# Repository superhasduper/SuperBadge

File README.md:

# SuperBadge
This is a remake of the PCB-badge. in collaboration with PCBway an incredible PCB Manufacturing company.
thanks to PCBway I have been able to remake the PCB badge I previously made and improve upon it a little.
PCBway is great for any prototypes or projects you may have in mind since it offers a lot different posibilities and configurations to customize and make your PCB just how you imagined it. It is very fast and of very high cuality(https://www.pcbway.com) check my instagram(@superhasduper)for pictures of the final product.You can also buy this pcb design directly from PCBway and forget about all the hastle and exporting gerber files and such(https://www.pcbway.com/project/shareproject/Superhasduper_superbadge.html)
This PCB was designed in kicad so I recommend viewing the files in kicad.

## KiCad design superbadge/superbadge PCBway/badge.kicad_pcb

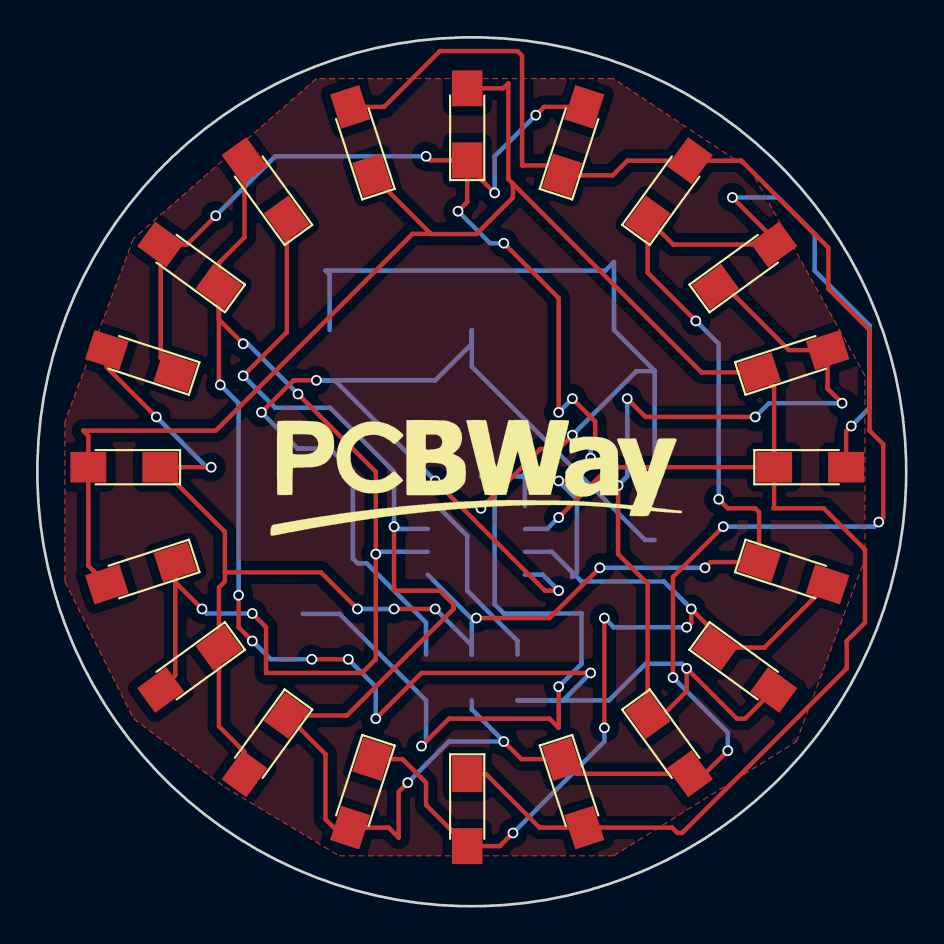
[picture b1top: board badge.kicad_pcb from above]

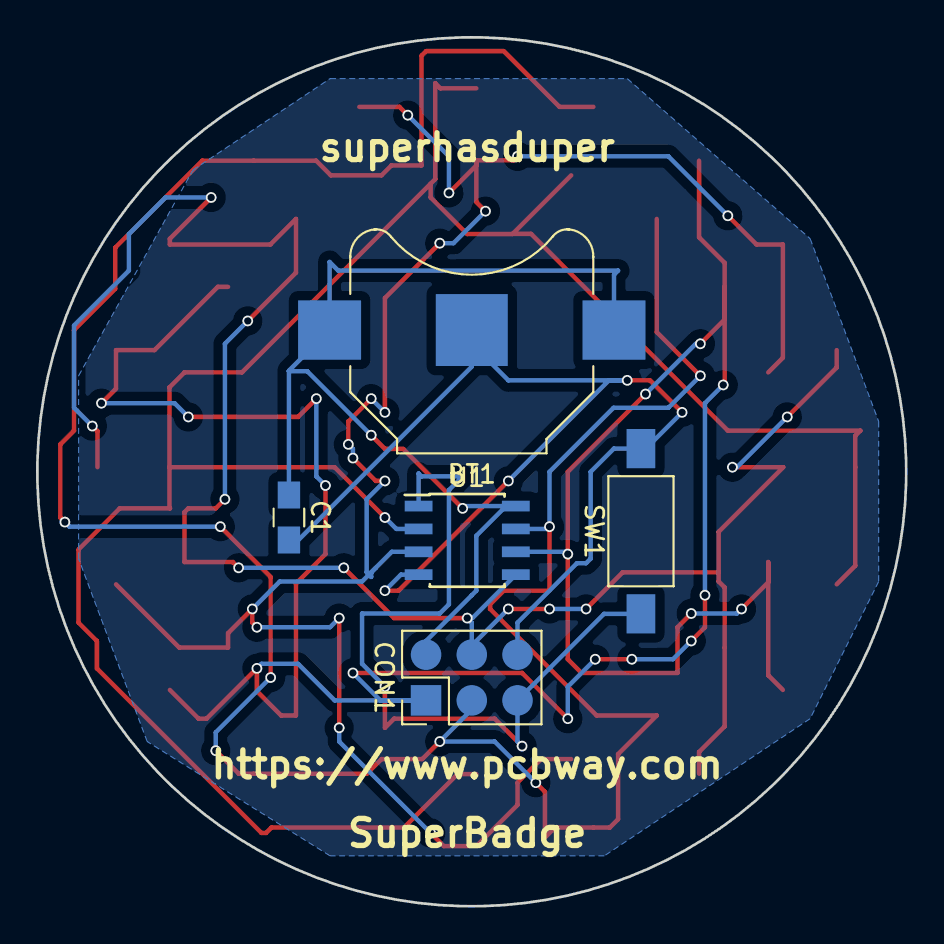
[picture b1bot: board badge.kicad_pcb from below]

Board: 2 copper layers, 48.3 x 48.3 mm, 25 parts (5 on the bottom side), 8 nets.

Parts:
BT1: Battery_Cell; Keystone_3000_1x12mm-CoinCell
C1: CP; C_0805_HandSoldering
CON1: AVR-ISP-6; Pin_Header_Straight_2x03_Pitch2.54mm
D1, D2, D3, D4, D5, D6, D7, D8, D9, D10, D11, D12, D13, D14, D15, D16, D17, D18, D19, D20: LED; LED_1206_HandSoldering
SW1: SW_Push; SW_SPST_FSMSM
U1: ATTINY85-20SU; SOIC-8_3.9x4.9mm_Pitch1.27mm

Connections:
+3V3: BT1.1, C1.1, CON1.2, U1.8
/MISO: CON1.1, D3.2, D4.1, D9.2, D10.1, D13.1, D14.2, D19.1, D20.2, U1.6
/MOSI: CON1.4, D1.2, D2.1, D8.2, D9.1, D11.1, D12.2, D18.1, D19.2, U1.5
/RESET: CON1.5, SW1.1, U1.1
/SCK: CON1.3, D4.2, D5.1, D7.2, D8.1, D14.1, D15.2, D17.1, D18.2, U1.7
GND: BT1.2, C1.2, CON1.6, SW1.2, U1.4
unnamed: D1.1, D5.2, D6.1, D10.2, D11.2, D15.1, D16.2, D20.1, U1.2
unnamed: D2.2, D3.1, D6.2, D7.1, D12.1, D13.2, D16.1, D17.2, U1.3

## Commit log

2019-09-27 update
    I just added a few things to the read me.
2019-09-27 all of the files for the PCB
    there are two PCBs attached one with my logo and the other with PCBway´s logo.
